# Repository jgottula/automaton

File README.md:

automaton
=========
`automaton` is a trip computer for your car. Utilizing breakthrough 1990s
technology, it will enable instantaeous visibility into various aspects of your
car's performance, such as engine data, fuel efficiency estimates, and speed
statistics. In addition, state-of-the-art SD card technology is now enabling the
sort of data logging and analysis that bored drivers of the past could only
dream about. `automaton` will undoubtably provide multiple hours of fun to
offset the innumerable hours its users spend driving.

what is it
----------
**Hardware** currently consists of a professionally fabricated PCB, mounted in a
sturdy project box with an RGB-backlit 128x64 graphics LCD for output and a
series of pushbuttons for input. IO connections on the board include **OBD-II**
(of course), **MicroSD** (for data logging), **MiniUSB** (for debug logging),
**JTAG** (for programming/debugging), and **PDI** (also for
programming/debugging).

**Firmware** consists of the AVR Xmega firmware program written in C that
operates the primary microcontroller.

**Software** will consist of PC-based Python scripts that can analyze logged
data to produce graphs and other statistical eye candy.

project status
--------------
**Hardware** is in its third version: first came the breadboard version that
used an AVR ATmega and the STN1110 OBD chip; second came a largely similar, but
more permanent, iteration built on perfboard; and now, the hardware is on a PCB
as described in the previous section. Hardware is essentially finalized, but a
second revision of the PCB may be produced if enough errata are found in the
first.

**Firmware** is where development is currently taking place. This is where most
of the work will be done, and a great deal of code needs to be ported over from
the older version.

**Software** is currently vaporware. Once the firmware is producing data, then
the software can be developed to analyze it.

supported vehicles
------------------
Vehicles must support OBD-II. Any vehicle made after 1996 is required by law to
implement OBD-II. However, the geniuses behind this standard decided that no
less than a half-dozen different physical layer implementations needed to be
developed to transmit the exact same information.

This means that vehicle support is limited by the type of bus in use. Vehicles
made after 2008 are required to support CAN (ISO 15765), so that is what the
current version of `automaton` supports. Future versions could feasibly support
more bus standards, pending developer motivation.

planned features
----------------

- Live data via LCD
- Deferred data analysis via micro SD card and Python scripts
- GPS waypoint logging
- Check Engine Light zapper
- Undocumented OBD-II PID sweeper

hardware and chips
------------------

Hardware is subject to change, but it's pretty locked down at this point.

- Microcontroller: Atmel ATxmega128A3U @ 32MHz (128KB flash; 8KB SRAM)
- CAN transceiver: Microchip MCP2562
- CAN controller: Microchip MCP2515
- Real-time clock: Maxim DS1390U
- GPS module: GlobalTop FGPMMOPA6H
- Debug UART: FTDI FT231XS
- LCD: 128x64 ST7565 graphic RGB-backlit LCD

compiling
---------
This project uses Avery Pennarun's implementation of D. J. Bernstein's `redo`
build system.

To build the `automaton` AVR firmware program, install `redo` and simply run
`redo all`. To clean the project directory, run `redo clean`.

To load the firmware onto the microcontroller, obtain a hardware programmer and
run `redo load`. You will almost certainly need to modify the build script for
this to work.

The build script may need to be modified for your system configuration. To do
so, you need only edit the `default.do` file in the project's root directory. As
`redo` uses posix shell scripts, a basic understanding of shell scripting is
sufficient to modify the build script to your purposes.

license
-------
This project is licensed under the terms of the simplified (2-clause) BSD
license. For more information, see the `LICENSE` file contained in the project's
root directory.

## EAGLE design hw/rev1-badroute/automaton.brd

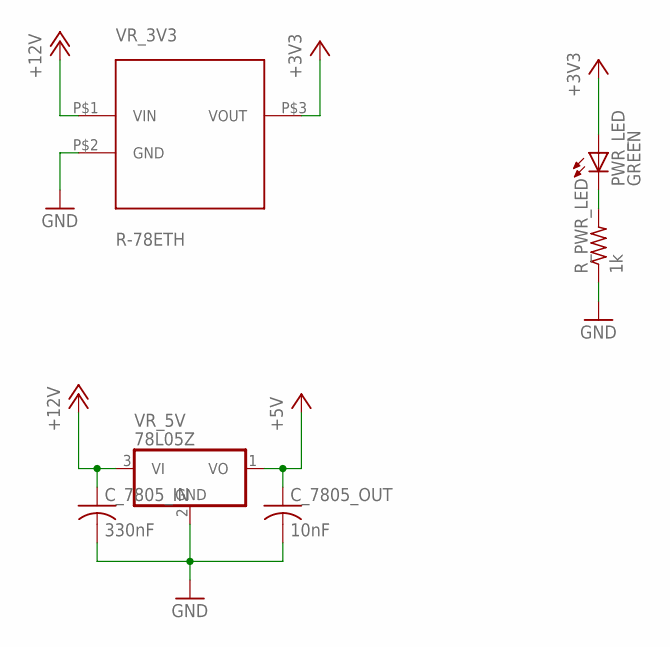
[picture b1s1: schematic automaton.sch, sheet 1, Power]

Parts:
C_7805_IN: 330nF; C1206
C_7805_OUT: 10nF; C1206
PWR_LED: GREEN; CHIPLED_1206
R_PWR_LED: 1k; R1206
VR_3V3: R-78ETH; R-78E
VR_5V: 78L05Z; TO92

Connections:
+3V3: PWR_LED.A, VR_3V3.P$3 (VOUT); also elsewhere on the board
+5V: C_7805_OUT.1, VR_5V.1 (VO); also elsewhere on the board
+12V: C_7805_IN.1, VR_3V3.P$1 (VIN), VR_5V.3 (VI); also elsewhere on the board
GND: C_7805_IN.2, C_7805_OUT.2, R_PWR_LED.1, VR_3V3.P$2 (GND), VR_5V.2 (GND); also elsewhere on the board
unnamed: PWR_LED.C, R_PWR_LED.2

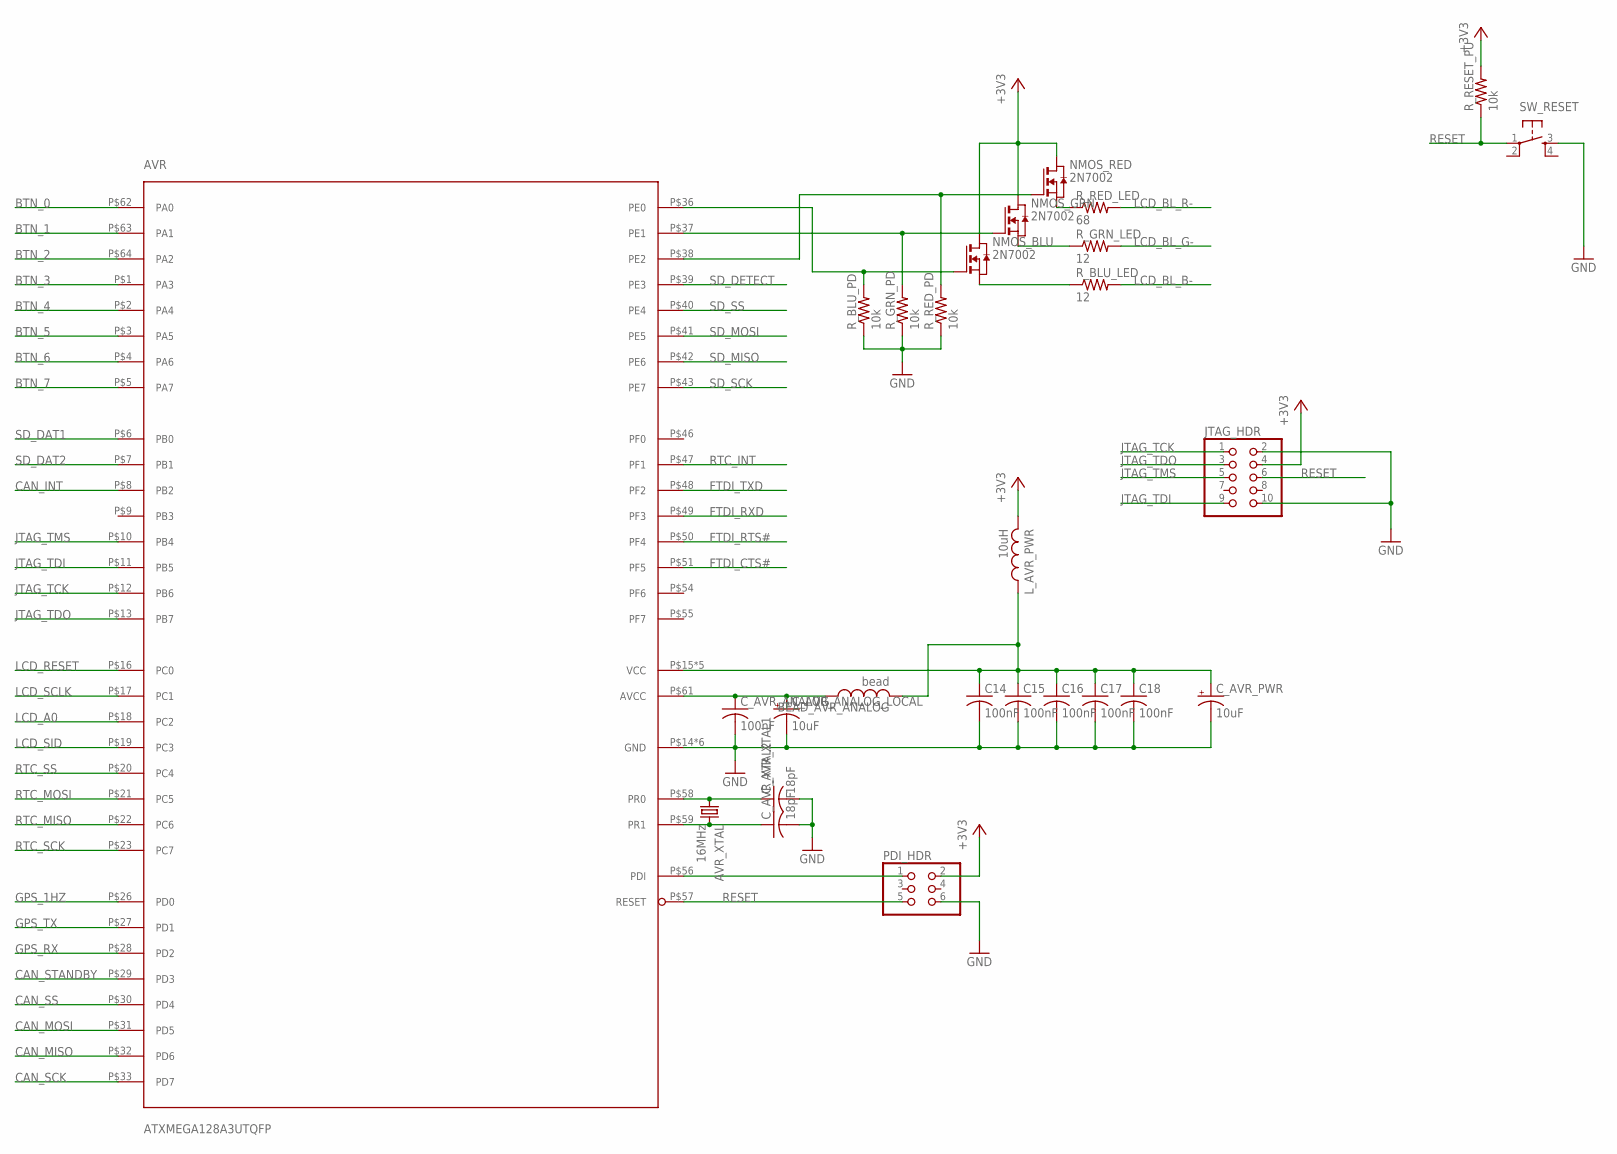
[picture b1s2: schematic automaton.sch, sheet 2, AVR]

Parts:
AVR: ATXMEGA128A3UTQFP; ATMEL_TQFP64
AVR_XTAL: 16MHz; HC49/S
BEAD_AVR_ANALOG: bead; L1812
C14, C15, C16, C17, C18: 100nF; C1206
C_AVR_ANALOG: 100nF; C1206
C_AVR_ANALOG_LOCAL: 10uF; E2-5
C_AVR_PWR: 10uF; E2-5
C_AVR_XTAL1, C_AVR_XTAL2: 18pF; C1206
JTAG_HDR: PINHD-2X05_2.54; 2X05
L_AVR_PWR: 10uH; L1812
NMOS_BLU: 2N7002; SOT-23
NMOS_GRN: 2N7002; SOT-23
NMOS_RED: 2N7002; SOT-23
PDI_HDR: PINHD-2X03_2.54; 2X03
R_BLU_LED: 12; R1206
R_BLU_PD: 10k; R1206
R_GRN_LED: 12; R1206
R_GRN_PD: 10k; R1206
R_RED_LED: 68; R1206
R_RED_PD: 10k; R1206
R_RESET_PU: 10k; R1206
SW_RESET: TAC_SWITCHSMD; TACTILE_SWITCH_SMD

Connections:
+3V3: JTAG_HDR.4, L_AVR_PWR.2, NMOS_BLU.1 (D), NMOS_GRN.1 (D), NMOS_RED.1 (D), PDI_HDR.2, R_RESET_PU.2; also elsewhere on the board
BTN_0: AVR.P$62 (PA0); also elsewhere on the board
BTN_1: AVR.P$63 (PA1); also elsewhere on the board
BTN_2: AVR.P$64 (PA2); also elsewhere on the board
BTN_3: AVR.P$1 (PA3); also elsewhere on the board
BTN_4: AVR.P$2 (PA4); also elsewhere on the board
BTN_5: AVR.P$3 (PA5); also elsewhere on the board
BTN_6: AVR.P$4 (PA6); also elsewhere on the board
BTN_7: AVR.P$5 (PA7); also elsewhere on the board
CAN_INT: AVR.P$8 (PB2); also elsewhere on the board
CAN_MISO: AVR.P$32 (PD6); also elsewhere on the board
CAN_MOSI: AVR.P$31 (PD5); also elsewhere on the board
CAN_SCK: AVR.P$33 (PD7); also elsewhere on the board
CAN_SS: AVR.P$30 (PD4); also elsewhere on the board
CAN_STANDBY: AVR.P$29 (PD3); also elsewhere on the board
FTDI_CTS#: AVR.P$51 (PF5); also elsewhere on the board
FTDI_RTS#: AVR.P$50 (PF4); also elsewhere on the board
FTDI_RXD: AVR.P$49 (PF3); also elsewhere on the board
FTDI_TXD: AVR.P$48 (PF2); also elsewhere on the board
GND: AVR.P$14 (GND), AVR.P$24 (GND), AVR.P$34 (GND), AVR.P$44 (GND), AVR.P$52 (GND), AVR.P$60 (GND), C14.2, C15.2, C16.2, C17.2, C18.2, C_AVR_ANALOG.2, C_AVR_ANALOG_LOCAL.-, C_AVR_PWR.-, C_AVR_XTAL1.2, C_AVR_XTAL2.2, JTAG_HDR.2, JTAG_HDR.10, PDI_HDR.6, R_BLU_PD.1, R_GRN_PD.1, R_RED_PD.1, SW_RESET.3; also elsewhere on the board
GPS_1HZ: AVR.P$26 (PD0); also elsewhere on the board
GPS_RX: AVR.P$28 (PD2); also elsewhere on the board
GPS_TX: AVR.P$27 (PD1); also elsewhere on the board
JTAG_TCK: AVR.P$12 (PB6), JTAG_HDR.1
JTAG_TDI: AVR.P$11 (PB5), JTAG_HDR.9
JTAG_TDO: AVR.P$13 (PB7), JTAG_HDR.3
JTAG_TMS: AVR.P$10 (PB4), JTAG_HDR.5
LCD_A0: AVR.P$18 (PC2); also elsewhere on the board
LCD_BL_B-: R_BLU_LED.2; also elsewhere on the board
LCD_BL_G-: R_GRN_LED.2; also elsewhere on the board
LCD_BL_R-: R_RED_LED.2; also elsewhere on the board
LCD_RESET: AVR.P$16 (PC0); also elsewhere on the board
LCD_SCLK: AVR.P$17 (PC1); also elsewhere on the board
LCD_SID: AVR.P$19 (PC3); also elsewhere on the board
unnamed: AVR.P$58 (PR0), AVR_XTAL.1, C_AVR_XTAL1.1
unnamed: AVR.P$59 (PR1), AVR_XTAL.2, C_AVR_XTAL2.1
unnamed: AVR.P$37 (PE1), NMOS_GRN.3 (G), R_GRN_PD.2
unnamed: AVR.P$36 (PE0), NMOS_BLU.3 (G), R_BLU_PD.2
unnamed: AVR.P$61 (AVCC), BEAD_AVR_ANALOG.1, C_AVR_ANALOG.1, C_AVR_ANALOG_LOCAL.+
unnamed: AVR.P$38 (PE2), NMOS_RED.3 (G), R_RED_PD.2
unnamed: AVR.P$15 (VCC), AVR.P$25 (VCC), AVR.P$35 (VCC), AVR.P$45 (VCC), AVR.P$53 (VCC), BEAD_AVR_ANALOG.2, C14.1, C15.1, C16.1, C17.1, C18.1, C_AVR_PWR.+, L_AVR_PWR.1
unnamed: NMOS_BLU.2 (S), R_BLU_LED.1
unnamed: NMOS_GRN.2 (S), R_GRN_LED.1
unnamed: NMOS_RED.2 (S), R_RED_LED.1
PDI_DATA: AVR.P$56 (PDI), PDI_HDR.1
RESET: AVR.P$57 (RESET), JTAG_HDR.6, PDI_HDR.5, R_RESET_PU.1, SW_RESET.1
RTC_INT: AVR.P$47 (PF1); also elsewhere on the board
RTC_MISO: AVR.P$22 (PC6); also elsewhere on the board
RTC_MOSI: AVR.P$21 (PC5); also elsewhere on the board
RTC_SCK: AVR.P$23 (PC7); also elsewhere on the board
RTC_SS: AVR.P$20 (PC4); also elsewhere on the board
SD_DAT1: AVR.P$6 (PB0); also elsewhere on the board
SD_DAT2: AVR.P$7 (PB1); also elsewhere on the board
SD_DETECT: AVR.P$39 (PE3); also elsewhere on the board
SD_MISO: AVR.P$42 (PE6); also elsewhere on the board
SD_MOSI: AVR.P$41 (PE5); also elsewhere on the board
SD_SCK: AVR.P$43 (PE7); also elsewhere on the board
SD_SS: AVR.P$40 (PE4); also elsewhere on the board

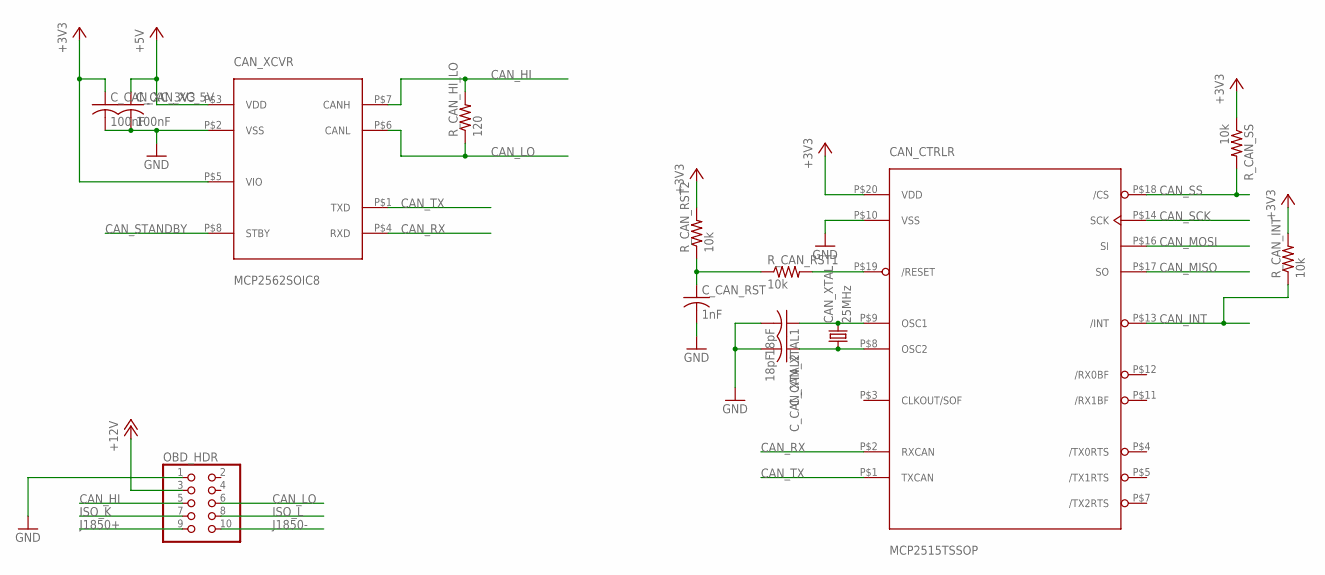
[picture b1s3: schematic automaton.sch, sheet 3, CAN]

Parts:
CAN_CTRLR: MCP2515TSSOP; MICROCHIP_TSSOP20
CAN_XCVR: MCP2562SOIC8; MICROCHIP_SOIC8
CAN_XTAL: 25MHz; HC49/S
C_CAN_RST: 1nF; C1206
C_CAN_XC_3V3, C_CAN_XC_5V: 100nF; C1206
C_CAN_XTAL1, C_CAN_XTAL2: 18pF; C1206
OBD_HDR: PINHD-2X05_2.54-90°; 2X05/90
R_CAN_HI_LO: 120; R1206
R_CAN_INT: 10k; R1206
R_CAN_RST1, R_CAN_RST2: 10k; R1206
R_CAN_SS: 10k; R1206

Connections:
+3V3: CAN_CTRLR.P$20 (VDD), CAN_XCVR.P$5 (VIO), C_CAN_XC_3V3.1, R_CAN_INT.2, R_CAN_RST2.2, R_CAN_SS.1; also elsewhere on the board
+5V: CAN_XCVR.P$3 (VDD), C_CAN_XC_5V.1; also elsewhere on the board
+12V: OBD_HDR.3; also elsewhere on the board
CAN_HI: CAN_XCVR.P$7 (CANH), OBD_HDR.5, R_CAN_HI_LO.2
CAN_INT: CAN_CTRLR.P$13 (/INT), R_CAN_INT.1; also elsewhere on the board
CAN_LO: CAN_XCVR.P$6 (CANL), OBD_HDR.6, R_CAN_HI_LO.1
CAN_MISO: CAN_CTRLR.P$17 (SO); also elsewhere on the board
CAN_MOSI: CAN_CTRLR.P$16 (SI); also elsewhere on the board
CAN_RX: CAN_CTRLR.P$2 (RXCAN), CAN_XCVR.P$4 (RXD)
CAN_SCK: CAN_CTRLR.P$14 (SCK); also elsewhere on the board
CAN_SS: CAN_CTRLR.P$18 (/CS), R_CAN_SS.2; also elsewhere on the board
CAN_STANDBY: CAN_XCVR.P$8 (STBY); also elsewhere on the board
CAN_TX: CAN_CTRLR.P$1 (TXCAN), CAN_XCVR.P$1 (TXD)
GND: CAN_CTRLR.P$10 (VSS), CAN_XCVR.P$2 (VSS), C_CAN_RST.2, C_CAN_XC_3V3.2, C_CAN_XC_5V.2, C_CAN_XTAL1.2, C_CAN_XTAL2.2, OBD_HDR.1; also elsewhere on the board
ISO_K: OBD_HDR.7
ISO_L: OBD_HDR.8
J1850+: OBD_HDR.9
J1850-: OBD_HDR.10
unnamed: C_CAN_RST.1, R_CAN_RST1.1, R_CAN_RST2.1
unnamed: CAN_CTRLR.P$9 (OSC1), CAN_XTAL.2, C_CAN_XTAL1.1
unnamed: CAN_CTRLR.P$8 (OSC2), CAN_XTAL.1, C_CAN_XTAL2.1
unnamed: CAN_CTRLR.P$19 (/RESET), R_CAN_RST1.2

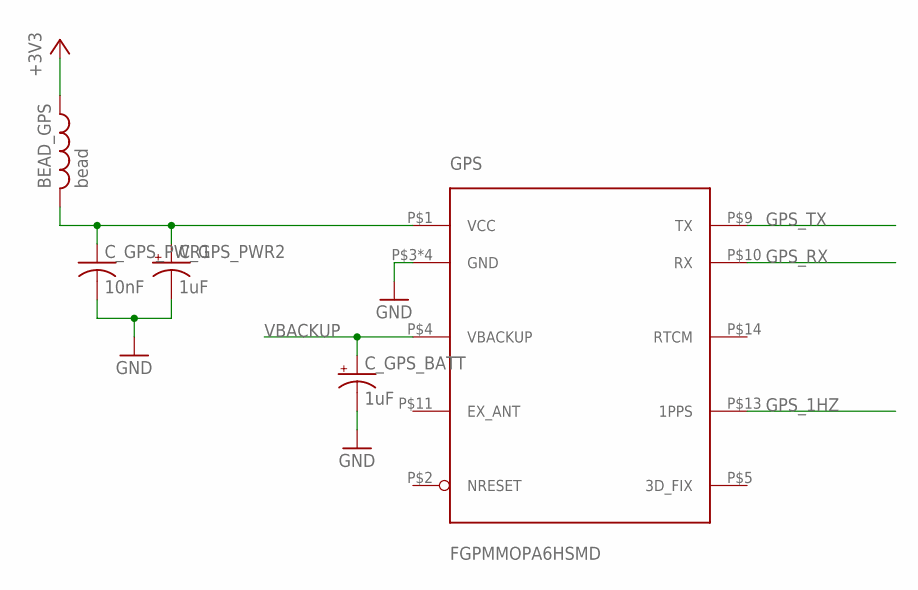
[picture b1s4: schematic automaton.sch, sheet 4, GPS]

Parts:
BEAD_GPS: bead; L1812
C_GPS_BATT: 1uF; E2-5
C_GPS_PWR1: 10nF; C1206
C_GPS_PWR2: 1uF; E2-5
GPS: FGPMMOPA6HSMD; FGPMMOPA6H

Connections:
+3V3: BEAD_GPS.1; also elsewhere on the board
GND: C_GPS_BATT.-, C_GPS_PWR1.2, C_GPS_PWR2.-, GPS.P$3 (GND), GPS.P$8 (GND), GPS.P$12 (GND), GPS.P$19 (GND); also elsewhere on the board
GPS_1HZ: GPS.P$13 (1PPS); also elsewhere on the board
GPS_RX: GPS.P$10 (RX); also elsewhere on the board
GPS_TX: GPS.P$9 (TX); also elsewhere on the board
unnamed: BEAD_GPS.2, C_GPS_PWR1.1, C_GPS_PWR2.+, GPS.P$1 (VCC)
VBACKUP: C_GPS_BATT.+, GPS.P$4 (VBACKUP); also elsewhere on the board

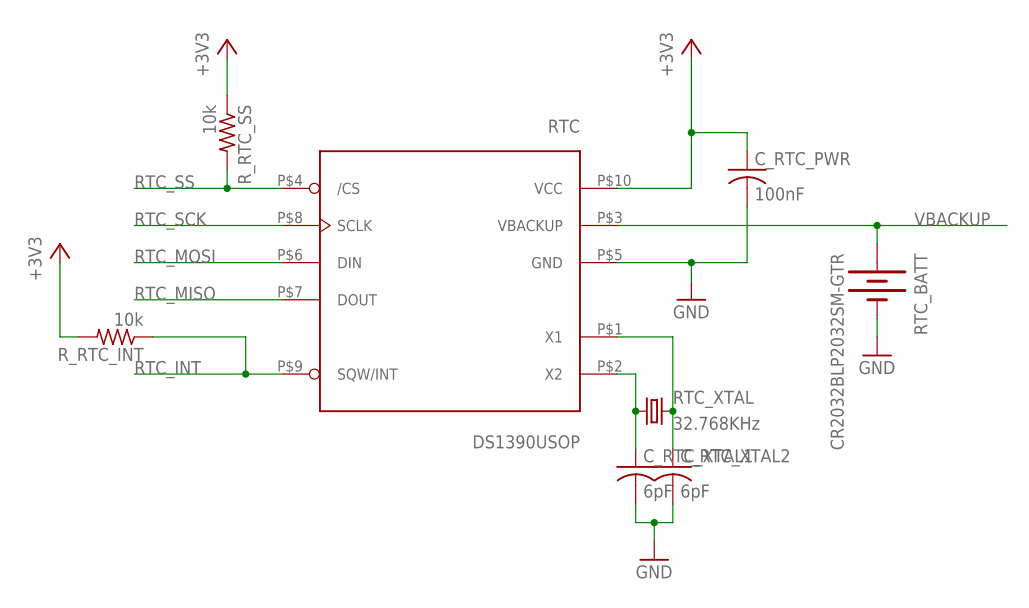
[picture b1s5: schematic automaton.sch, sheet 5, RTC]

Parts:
C_RTC_PWR: 100nF; C1206
C_RTC_XTAL1, C_RTC_XTAL2: 6pF; C1206
RTC: DS1390USOP; MAXIM_10USOP
RTC_BATT: CR2032BLP2032SM-GTR; BLP2032SM-GTR
RTC_XTAL: 32.768KHz; TC26V
R_RTC_INT: 10k; R1206
R_RTC_SS: 10k; R1206

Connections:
+3V3: C_RTC_PWR.1, RTC.P$10 (VCC), R_RTC_INT.2, R_RTC_SS.1; also elsewhere on the board
GND: C_RTC_PWR.2, C_RTC_XTAL1.2, C_RTC_XTAL2.2, RTC.P$5 (GND), RTC_BATT.P$2 (-); also elsewhere on the board
unnamed: C_RTC_XTAL1.1, RTC.P$2 (X2), RTC_XTAL.1
unnamed: C_RTC_XTAL2.1, RTC.P$1 (X1), RTC_XTAL.2
RTC_INT: RTC.P$9 (SQW/INT), R_RTC_INT.1; also elsewhere on the board
RTC_MISO: RTC.P$7 (DOUT); also elsewhere on the board
RTC_MOSI: RTC.P$6 (DIN); also elsewhere on the board
RTC_SCK: RTC.P$8 (SCLK); also elsewhere on the board
RTC_SS: RTC.P$4 (/CS), R_RTC_SS.2; also elsewhere on the board
VBACKUP: RTC.P$3 (VBACKUP), RTC_BATT.P$1 (+); also elsewhere on the board

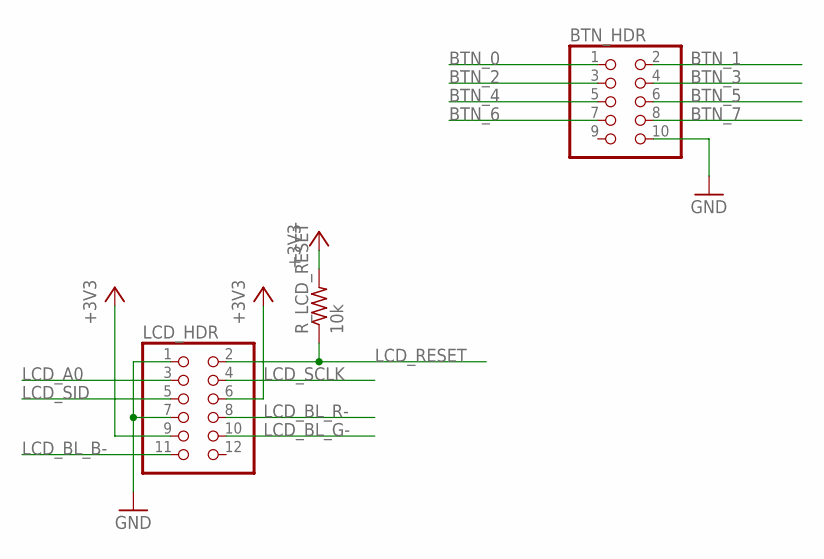
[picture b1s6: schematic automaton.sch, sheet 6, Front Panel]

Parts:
BTN_HDR: PINHD-2X05_2.54; 2X05
LCD_HDR: PINHD-2X06_2.54; 2X06
R_LCD_RESET: 10k; R1206

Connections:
+3V3: LCD_HDR.6, LCD_HDR.9, R_LCD_RESET.2; also elsewhere on the board
BTN_0: BTN_HDR.1; also elsewhere on the board
BTN_1: BTN_HDR.2; also elsewhere on the board
BTN_2: BTN_HDR.3; also elsewhere on the board
BTN_3: BTN_HDR.4; also elsewhere on the board
BTN_4: BTN_HDR.5; also elsewhere on the board
BTN_5: BTN_HDR.6; also elsewhere on the board
BTN_6: BTN_HDR.7; also elsewhere on the board
BTN_7: BTN_HDR.8; also elsewhere on the board
GND: BTN_HDR.10, LCD_HDR.1, LCD_HDR.7; also elsewhere on the board
LCD_A0: LCD_HDR.3; also elsewhere on the board
LCD_BL_B-: LCD_HDR.11; also elsewhere on the board
LCD_BL_G-: LCD_HDR.10; also elsewhere on the board
LCD_BL_R-: LCD_HDR.8; also elsewhere on the board
LCD_RESET: LCD_HDR.2, R_LCD_RESET.1; also elsewhere on the board
LCD_SCLK: LCD_HDR.4; also elsewhere on the board
LCD_SID: LCD_HDR.5; also elsewhere on the board

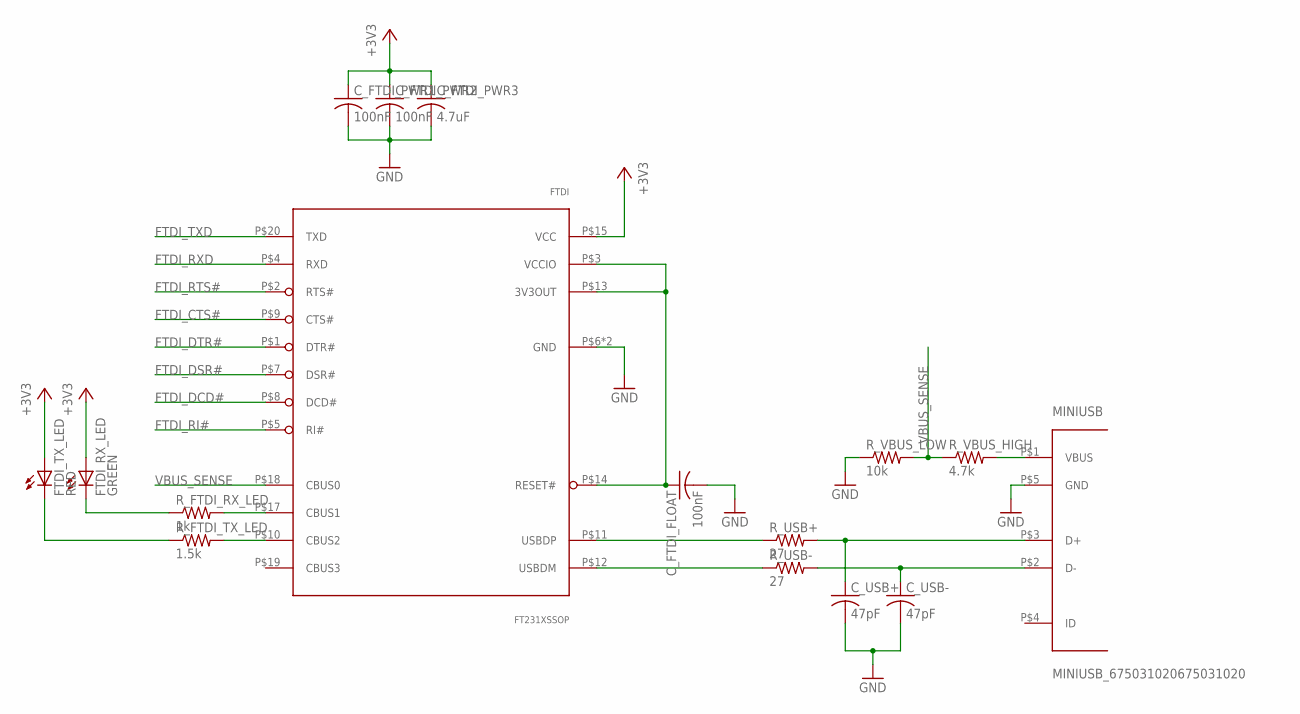
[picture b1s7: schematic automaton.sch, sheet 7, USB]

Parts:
C_FTDI_FLOAT: 100nF; C1206
C_FTDI_PWR1, C_FTDI_PWR2: 100nF; C1206
C_FTDI_PWR3: 4.7uF; C1206
C_USB+: 47pF; C1206
C_USB-: 47pF; C1206
FTDI: FT231XSSOP; FTDI_SSOP20
FTDI_RX_LED: GREEN; CHIPLED_1206
FTDI_TX_LED: RED; CHIPLED_1206
MINIUSB: MINIUSB_675031020675031020; MINIUSB_675031020
R_FTDI_RX_LED: 1k; R1206
R_FTDI_TX_LED: 1.5k; R1206
R_USB+: 27; R1206
R_USB-: 27; R1206
R_VBUS_HIGH: 4.7k; R1206
R_VBUS_LOW: 10k; R1206

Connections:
+3V3: C_FTDI_PWR1.1, C_FTDI_PWR2.1, C_FTDI_PWR3.1, FTDI.P$15 (VCC), FTDI_RX_LED.A, FTDI_TX_LED.A; also elsewhere on the board
FTDI_CTS#: FTDI.P$9 (CTS#); also elsewhere on the board
FTDI_DCD#: FTDI.P$8 (DCD#)
FTDI_DSR#: FTDI.P$7 (DSR#)
FTDI_DTR#: FTDI.P$1 (DTR#)
FTDI_RI#: FTDI.P$5 (RI#)
FTDI_RTS#: FTDI.P$2 (RTS#); also elsewhere on the board
FTDI_RXD: FTDI.P$4 (RXD); also elsewhere on the board
FTDI_TXD: FTDI.P$20 (TXD); also elsewhere on the board
GND: C_FTDI_FLOAT.2, C_FTDI_PWR1.2, C_FTDI_PWR2.2, C_FTDI_PWR3.2, C_USB+.2, C_USB-.2, FTDI.P$6 (GND), FTDI.P$16 (GND), MINIUSB.P$5 (GND), R_VBUS_LOW.1; also elsewhere on the board
unnamed: C_FTDI_FLOAT.1, FTDI.P$3 (VCCIO), FTDI.P$13 (3V3OUT), FTDI.P$14 (RESET#)
unnamed: FTDI_RX_LED.C, R_FTDI_RX_LED.1
unnamed: FTDI.P$12 (USBDM), R_USB-.1
unnamed: FTDI.P$11 (USBDP), R_USB+.1
unnamed: FTDI_TX_LED.C, R_FTDI_TX_LED.1
unnamed: FTDI.P$10 (CBUS2), R_FTDI_TX_LED.2
unnamed: FTDI.P$17 (CBUS1), R_FTDI_RX_LED.2
unnamed: C_USB+.1, MINIUSB.P$3 (D+), R_USB+.2
unnamed: C_USB-.1, MINIUSB.P$2 (D-), R_USB-.2
unnamed: MINIUSB.P$1 (VBUS), R_VBUS_HIGH.2
VBUS_SENSE: FTDI.P$18 (CBUS0), R_VBUS_HIGH.1, R_VBUS_LOW.2

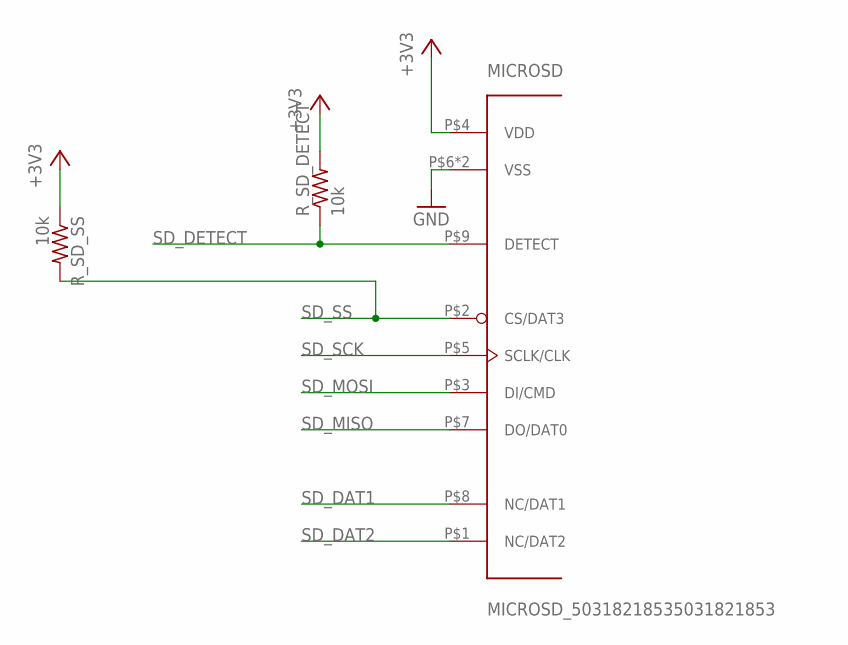
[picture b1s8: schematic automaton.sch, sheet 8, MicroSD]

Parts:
MICROSD: MICROSD_50318218535031821853; MICROSD_5031821853
R_SD_DETECT: 10k; R1206
R_SD_SS: 10k; R1206

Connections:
+3V3: MICROSD.P$4 (VDD), R_SD_DETECT.2, R_SD_SS.1; also elsewhere on the board
GND: MICROSD.P$6 (VSS), MICROSD.P$10 (VSS); also elsewhere on the board
SD_DAT1: MICROSD.P$8 (NC/DAT1); also elsewhere on the board
SD_DAT2: MICROSD.P$1 (NC/DAT2); also elsewhere on the board
SD_DETECT: MICROSD.P$9 (DETECT), R_SD_DETECT.1; also elsewhere on the board
SD_MISO: MICROSD.P$7 (DO/DAT0); also elsewhere on the board
SD_MOSI: MICROSD.P$3 (DI/CMD); also elsewhere on the board
SD_SCK: MICROSD.P$5 (SCLK/CLK); also elsewhere on the board
SD_SS: MICROSD.P$2 (CS/DAT3), R_SD_SS.2; also elsewhere on the board

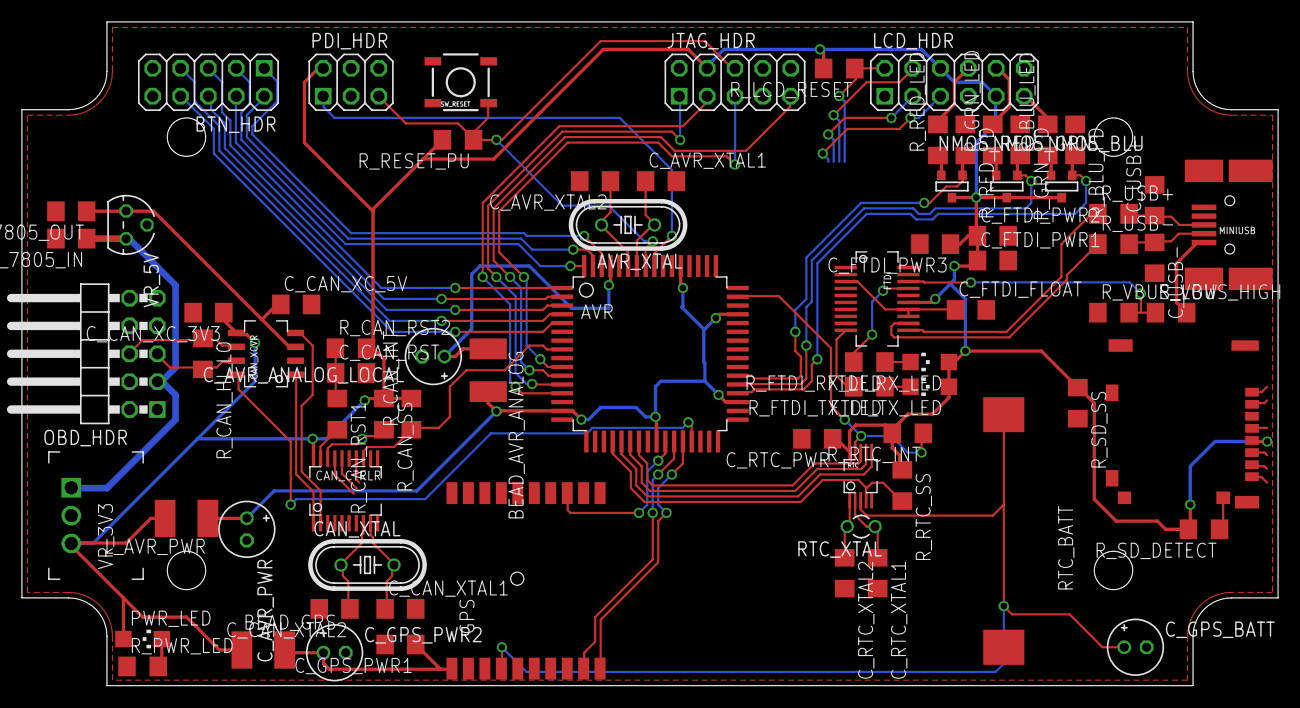
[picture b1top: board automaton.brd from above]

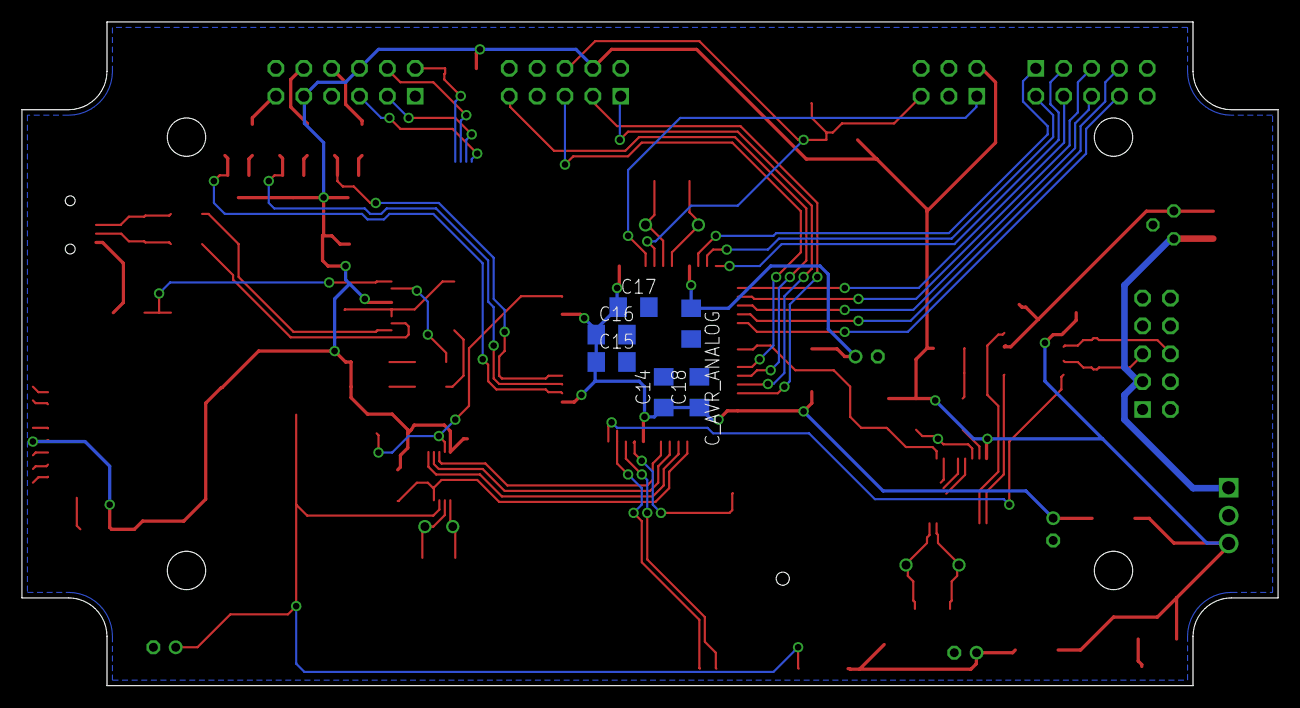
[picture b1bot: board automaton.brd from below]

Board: 2 copper layers, 114.5 x 60.5 mm, 82 parts (6 on the bottom side), 84 nets.

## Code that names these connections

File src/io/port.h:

/* automaton
 * (c) 2014 Justin Gottula
 * The source code of this project is distributed under the terms of the
 * simplified BSD license. See the LICENSE file for details.
 */


#ifndef AUTOMATON_IO_PORT_H
#define AUTOMATON_IO_PORT_H


#include "std.h"


//#define REG_MODIFY(_reg, _mask, _val) \
// 	(_reg) = (((_reg) & ~(_mask)) | ((_val) & (_mask)))


/* pinout:
PA0-7: BTN_0-7

PB0: SD_DAT1
PB1: SD_DAT2
PB2: CAN_INT
PB4-7: JTAG_TMS, _TDI, _TCK, _TDO

PC0-3: LCD_RESET, _SCK, _A0, _SID
PC4-7: RTC_SS, _MOSI, _MISO, _SCK
USARTC0 (SPI master mode): LCD
SPIC: RTC

PD0: GPS_1HZ
PD1: CAN_STANDBY
PD2-3: GPS_TX, _RX
PD4-7: CAN_SS, _MOSI, _MISO, _SCK
USARTD0: GPS
SPID: CAN

PE0-2: LCD_BL_B-, _G-, _R-
PE3-7: SD_DETECT, _SS, _MOSI, _MISO, _SCK
SPIE: SD

PF1: RTC_INT
PF2-5: FTDI_TXD, _RXD, _RTS#, _CTS#
USARTF0: FTDI
*/


#if 0
#define DDR(_x) \
	CONCAT(DDR, _x)
#define PORT(_x) \
	CONCAT(PORT, _x)
#define PIN(_x) \
	CONCAT(PIN, _x)


#define IO_LCD_BUS  A
#define IO_BTN      A
#define IO_RTC      B
#define IO_SD       B
#define IO_SPI      B
#define IO_LED      D
#define IO_LCD_CTRL D


enum io_port_a {
	IO_LCD_BUS_ALL = _BV(PA0) | _BV(PA1) | _BV(PA2) | _BV(PA3),
	
	/* these must be contiguous */
	IO_BTN_A     = _BV(PA4),
	IO_BTN_B     = _BV(PA5),
	IO_BTN_C     = _BV(PA6),
	IO_BTN_D     = _BV(PA7),
	IO_BTN_ALL   = IO_BTN_A | IO_BTN_B | IO_BTN_C | IO_BTN_D,
	IO_BTN_FIRST = IO_BTN_A,
};

enum io_port_b {
	IO_RTC_IO   = _BV(PB0),
	IO_RTC_SCLK = _BV(PB1),
	IO_RTC_CE   = _BV(PB2),
	IO_RTC_ALL  = IO_RTC_IO | IO_RTC_SCLK | IO_RTC_CE,
	
	IO_SD_DETECT = _BV(PB3),
	
	/* warning: don't set PB4 as input, or spi master mode may be disabled */
	IO_SPI_SS_SD  = _BV(PB4),
	IO_SPI_SS_ALL = IO_SPI_SS_SD,
	
	IO_SPI_MOSI = _BV(PB5),
	IO_SPI_MISO = _BV(PB6),
	IO_SPI_SCK  = _BV(PB7),
	IO_SPI_ALL  = IO_SPI_MOSI | IO_SPI_MISO | IO_SPI_SCK,
};

/*enum io_port_c {*/
	/* PC2: JTAG */
	/* PC3: JTAG */
	/* PC4: JTAG */
	/* PC5: JTAG */
/*};*/

enum io_port_d {
	/* PD0: UART0 rx */
	/* PD1: UART0 tx */
	/* PD2: UART1 rx */
	/* PD3: UART1 tx */
	
	IO_LCD_CTRL_E   = _BV(PD4),
	IO_LCD_CTRL_RW  = _BV(PD5),
	IO_LCD_CTRL_RS  = _BV(PD6),
	IO_LCD_CTRL_ALL = IO_LCD_CTRL_E | IO_LCD_CTRL_RW | IO_LCD_CTRL_RS,
	
	IO_LED_0   = _BV(PD7),
	IO_LED_ALL = IO_LED_0,
};
#endif


#endif

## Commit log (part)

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2013-03-26 initial: add license
2013-03-27 initial: add gitignore
2013-03-27 redo: adapt preliminary redo script from jgfs2 and AVRm68k
2013-03-27 redo: fix typo in output filenames
2013-03-27 redo: only dump .text section
2013-03-27 io: replace inline functions with preprocessor macros
2013-03-27 src: move common library headers into subdirectory
2013-03-27 lcd: write init routine
2013-03-27 redo: add -F flag to avrdude invocation to avoid device id issues
2013-03-28 src: restructure include headers
2013-03-29 uart: implement basic functionality
2013-03-29 debug: add reset function
2013-03-29 src: make the lcd work
2013-04-06 time/alarm: implement timeout alarm using TIMER1
2013-04-07 algo/fifo: make fifo_{count,free} internal
2013-04-07 io/uart: implement uart_flush
2013-04-07 algo/fifo: make fifo_{count,free} public again
2013-04-07 src: restructure source files
2013-04-07 redo: don't use ccache
2013-04-07 redo: add *.lst output with source lines mixed in with disassembly
2013-04-07 io/uart: add missing dev param to uart_write_pstr macro
2013-04-07 time/alarm: reduce code size by factoring out alarm_unset
2013-04-07 io/uart: remove code gen warning
2013-04-07 io/uart: return characters read in all uart_{read,write}_*
2013-04-07 main: open stdin and stdout
2013-04-07 std includes: add <stdio.h>
2013-04-07 redo: add -mcall-prologues, -mrelax, -mstrict-X
2013-04-07 redo: add -Waddr-space-convert
2013-04-07 redo: add -ffast-math
2013-04-07 io/uart: remove non-character functions
2013-04-07 io/uart: reorder uart_divisor members
2013-04-07 io/spi: implement spi
2013-04-07 doc/todo: update for progress made
2013-04-07 lcd/hd44780: implement file functionality; ditch non-char functions
2013-04-07 doc/todo: fix typo; add test coverage item
2013-04-07 README: adapt from jgfs2
2013-04-07 debug/assert: implement assert
2013-04-07 doc/todo: restructure and add new items
2013-04-07 README: increase pessimism wrt board manufacture
2013-04-07 lcd: restructure to improve high-/low-level abstraction
2013-04-07 lcd/lcd: finish updating for new state structure
2013-04-07 lcd/hd44780: revamp data read/write functions to handle hd44780 quirks
2013-04-07 lcd/lcd: update for modified hd44780 data write function
2013-04-07 lcd/lcd: add char and file read ability
2013-04-08 io/led: add basic led debugging ability (and LED_BLOCK hackery)
2013-04-12 redo: fix broken 'set -e' functionality in redo
2013-04-12 doc/todo: add several areas of note
2013-04-12 lib/FatFs: import ELM FatFs library for fat32
2013-04-12 lib/FatFs: fix -Wcomment in option/syscall.c
2013-04-12 lib: add fat library candidates
2013-04-12 algo/fifo: use nonvolatile fifo ptr in fifo_internal_*
2013-04-12 lcd/lcd: add lcd_clear
2013-04-12 io/io: add DS1302 spi ss line
2013-04-12 io/uart: rename UART_DEBUG to UART_PC
2013-04-12 algo/fifo: alleviate volatile pointer cast warnings
2013-04-12 io/uart: add uart_avail prototype to header
2013-04-12 io/uart: add fifo and interrupt count debug code
2013-04-12 io/uart: disable fifo debugging
2013-04-12 io/uart: move debug definitions below includes
2013-04-13 algo/fifo: fix whitespace
2013-04-13 io/uart: include lcd header regardless of debug status
2013-04-13 io/uart: remove needless duplication of fifo calls
2013-04-13 io/uart: reorder tx operations; don't prime the pump
2013-04-13 io/uart: eliminate tx wait stuff
2013-04-13 redo: remove retry code in load (incompatible with set -e)
2013-04-13 storage/fatfs: rename; add get_fattime stub
2013-04-13 io/uart: do clear the lcd before writing for fifo debugging
2013-04-13 io/uart: add some more int flag debug statements
2013-04-13 std: add <ctype.h>
2013-04-13 doc/todo: update and reformat
2013-04-14 redo: use -fno-jump-tables
2013-04-14 redo: use -fshort-enums
2013-04-17 cfg: add configuration files for atmega324a, dragon_jtag, usbasp
2013-04-18 cfg/atmega324a: switch to full-swing oscillator (fixed sporadic issues)
2013-04-18 io/io: add comments for reserved pins
2013-04-18 debug/assert: use _BREAK()
2013-04-18 debug/reset: remove reset_defuse
2013-04-18 debug/stdfile: combine fdevopen/fclose for standard streams
2013-04-18 io/uart: handle LF/CR transformations in stdfile wrappers
2013-04-18 obd/stn1110: transform \r to \n and back
2013-04-18 io/io: correct PAx unused comments
2013-04-19 redo: add dependency on configuration files
2013-04-20 io/spi: add clock divider constants for 10 MHz
2013-04-20 io/uart: fix 115200 baud divisor for 10 MHz
2013-04-20 io/uart: add baud divisors for 300, 600, 1200 baud
2013-04-20 io/uart: add note regarding clearing of state upon re-init
2013-04-20 debug/die: wait 1000ms for uart flush
2013-04-23 redo: tweak some stuff
2013-04-23 cfg: put type in header comment
2013-04-23 doc/todo: add several more ideas
2013-04-23 test: create some rough test scripts
2013-04-23 time/alarm: assert to protect against double-arm condition
2013-04-23 uart/uart: move from io/uart
2013-04-23 debug/assert: make use of uart/direct
2013-04-23 debug/assert: add newline before assertion failure statement
2013-04-24 lib: add avrfix
2013-04-25 lcd: fix local addr not being updated after every char
2013-04-25 obd/stn1110: implement some rudimentary command support
2013-04-27 lcd/lcd: send address to fix new 4x20 row bug
2013-04-27 time/timer0: implement generic millisecond timer
2013-04-27 time/alarm: remove unused alarm rewrite code
2013-04-27 uart/uart: update for alarm and fifo changes
2013-04-27 time/alarm: rename first; fix wrong initial prev_next in unregister
2013-04-27 obd/stn1110: make timeout name consistent with changes elsewhere
2013-04-27 lcd/lcd: rename state struct
2013-04-27 common/macro: add CEIL, ROUND
2013-04-27 button/button: implement robust button system
2013-04-27 io/io: define button pins
2013-04-27 main: bring up to date
2013-04-27 time/alarm: add explanatory note to alarm_stop
2013-04-27 button/button: set pullups before input mode
2013-04-27 lcd/hd44780: set pullups before input mode
2013-04-27 io/io: rename io_read and io_write macros to IO_READ and IO_WRITE
2013-04-27 time/delay: write new, programmable nanosecond delay macro
2013-04-27 lcd/hd44780: make bus cycles atomic
2013-04-27 lcd/hd44780: fix scope error due to ATOMIC_BLOCK insertion
2013-04-27 rtc/ds1302: implement 3-wire protocol via bitbang
2013-04-27 time/timer0: rename hooks called by timer0 isr
2013-04-27 io/io: define io's for ds1302 bitbang
2013-04-27 obd/stn1110: implement timeouts, state struct
2013-04-27 std: include <time.h> from latest avr-libc
2013-04-27 debug/reset: bring back reset_defuse
2013-04-27 rtc/ds1302: fix pullups being enabled on IO
2013-04-27 rtc/ds1302: remove debug printf's
2013-04-27 rtc/ds1302: implement burst mode
2013-04-27 rtc/ds1302: rename CK register enum values
2013-04-28 conv/bcd: implement 8-bit packed bcd encoding and decoding
2013-04-28 time/clock: load system time at init, and tick thereafter
2013-04-28 rtc/rtc: implement rtc_set_tm
2013-04-28 storage/fatfs: add a reminder to use <time.h> fatfs_time
2013-04-28 ui/ui: make some ugly changes
2013-04-28 conv/hex: add some stubs
2013-04-28 main: put time demo on lcd
2013-04-28 ui: implement paged ui system
2013-04-28 lcd/lcd: replace xy cursor handling with rc
2013-04-28 lcd/lcd: fix typo in xy to rc conversion
2013-04-29 lcd/lcd: make state structs static
2013-04-29 ui/time: adjust behavior of time stoppage during setting
2013-04-29 ui/time: change min year to 100 (2000)
2013-04-29 rtc/rtc: add debug statements
2013-04-29 button/button: rename button_event function to button_pump
2013-04-29 ui: restructure so the primary loop is in ui/ui
2013-04-30 io/spi: remove per-device parameters in header
2013-04-30 ui: adjust header format
2013-04-30 algo/crc7: fix not using pgm_read_byte in table access
2013-04-30 sd: break down into layers in separate directory
2013-05-01 redo: add avrdude verify target
2013-08-31 cfg/mcu: add atmega1284p configuration
2013-08-31 io/io: modify pins for revision 2 hardware (perfboard)
2013-08-31 doc/todo: add power saving items
2013-08-31 ui: use symbolic button number names
2013-09-07 cfg/mcu: change CPU freqency to 8 MHz
2013-09-07 io/spi: add 8 MHz bit rate dividers
2014-02-12 check in version 3 changes
2014-02-13 README: correct LCD resolution
2014-02-13 mcu/clock: split into setup and use functions
2014-02-13 dev/button: move button code over
2014-02-13 io/port: fix LCD_BL_{R,B}- order
2014-02-13 dev/lcd/backlight: implement PWM for fadey RGB awesomeness
2014-02-14 dev/lcd/st7565: shorten command names
2014-02-14 std: add <avr/cpufunc.h> for _NOP
2014-02-14 main: add sprite test
2014-02-14 dev/lcd/font: add 04b_03 font and character drawing functions
2014-02-14 main: add font test
2014-02-14 dev/lcd/font_04b_03: remove "check this" on space length
2014-02-14 mcu/mem: add safe calloc; use attribute __malloc__ on both functions
2014-02-14 mcu/clock: use CPU_CCP rather than CCP
2014-02-27 dev/uart/direct: delete
2014-02-27 dev/lcd/spi: improve USART init as per manual
2014-02-27 algo/fifo: put atomic responsibility onto fifo_ function callers
2014-02-27 debug/assert: add ASSERT_FAIL_BREAK; use interrupt-driven UART functions
2014-02-27 mcu/die: clean up for rewritten UART functionality
2014-02-27 mcu/reset: make consistent with changes to mcu/die
2014-02-27 dev/uart/uart: rewrite and simplify for FTDI use only
2014-03-10 dev/uart/uart: fix bad math for BSCALE in BAUDCTRLB
2014-03-10 algo/fifo: fix double-increment of indexes in push and pop
2014-03-10 dev/lcd/font: add CR and NL support
2014-03-10 mcu/pmic: add pmic_init to fully enable interrupts
2014-03-10 dev/uart/uart: handle DRE interrupt flag differently
2014-03-10 dev/uart/uart: set FTDI CTS# low in uart_init
2014-03-10 dev/uart/uart: change RXC int priority from high to medium
2014-03-10 dev/can/spi: implement basic SPI functions for MCP2515 use
2014-03-11 io/port: fix incorrect PORTD assignments
2014-03-11 dev/can/can: implement basic MCP2515 SPI command functionality
2014-03-11 main: add die() to end so things get flushed properly
2014-03-11 dev/uart/stdfile: add lcd file
2014-03-11 std: add io/stdfile.h
2014-03-11 main: remove dev/uart/stdfile.h inclusion
2014-03-26 obd/obd: perform OBD-II mode 01 pid 00 test
2014-03-26 main: call OBD test
2014-03-26 dev/can: factor out bitrate setting; cleanups
2014-03-26 obd/obd: use new can_init; cleanups
2014-03-26 obd/obd: fix pointer error
2014-03-26 dev/can: move config mode setting into bit timing setup function
2014-03-26 dev/can/mcp2515: enable rx rollover
2014-03-26 dev/can/mcp2515: add mcp2515_choose_tx_buf
2014-03-27 dev/can/mcp2515: add struct mcp_[rt]x_buf and use in functions
2014-03-27 obd/obd: use new can_msg struct with can_tx
2014-03-27 dev/can/mcp2515: receive frames into a fifo
2014-03-27 obd/obd: add obd_query; perform PID support enumeration
2014-03-27 dev/can/mcp2515: make mcp2515_get_rx_buf interrupt-safe
2014-03-27 hw/rev1-errata: add LED erratum
2014-03-27 dev/button/button: add some preliminary nonfunctional code
2014-03-27 dev/lcd/font_04b_03: double width of space character
2014-03-27 dev/can/mcp2515: fix spelling in comment
2014-03-29 redo: add -fno-inline to debug options to make debugging easier
2014-03-29 debug/fatal: add new fatal function
2014-03-29 dev/lcd/font: add lcd_set_cur
2014-03-29 std: add debug/fatal.h
2014-03-29 dev/can/can: fix temporary intentional memory leak
2014-03-29 dev/can/mcp2515: silence some lcd chatter
2014-03-29 main: cosmetic changes
2014-03-29 obd/obd: revert to old handling in obd_query
2014-03-29 obd/obd: temporarily disable pid support checking
2014-03-29 debug/assert: revert addition of __func__ because gcc is retarded
2014-04-11 dev/can/can: remove duplicate assignment
2014-04-15 dev/lcd/gfx: implement pixel, line and rectangle gfx functions
2014-04-15 dev/can/mcp2515: temporarily use one-shot mode to avoid errors

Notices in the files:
parts and their libraries:
SparkFun: Licensing: CC v3.0 Share-Alike You are welcome to use this library for commercial purposes.
